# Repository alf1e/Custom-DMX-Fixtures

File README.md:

# Alfie's Custom DMX Fixtures
## What is this?
This project contains any relevant files for Custom DMX Fixtures project. In this repository you can find a PCB controller board, compatible with Neopixel LEDs using WLED. A fixture board which converts the signal sent from the controller to something usable by the Neopixel strip. And a LED Bar Fixture using the 24V version of the fixture control board.

## Why did you make this?
I volunteer at my school running our lighting rig for our shows. After one show in February, I realised something was missing and that it would look awesome with some kind of bar fixture. So I started this project and here we are now :D

# Images
Here are some relevant pictures of my project. Ill add more as I have then and as is needed.

## Control Board

## 24V Fixture Board

# Firmware
For the firmware, you can use any compilation of WLED with DMX enabled.

You can compile WLED at [this website](https://wled-compile.github.io/?lang=en) using my config file in the root of this repository called `firmware.json`

# External Wiring
A DMX Fixture is basically a fancy name for a software controlled light, usually in a theatrical setting. My Fixtures are connected to the controlled using a GX12-4 cable matching 24V with 24V, A with LED-, B with LED+ and GND with GND. Relatively simple!

# How to use.
Once you have the firmware installed there is 2 ways you can use this.

## No DMX
This can be purely controlled by any WLED control software. For mobile, I use WLED Native or just go to the IP of the controller on desktop. You can then change the colour and set effects through here

## DMX
This is a bit more complicated. Once you have connected the controller to your computer via a DMX interface you can open any DMX control software like QLC+ and import the configuration of the lights (Coming soon! I cant create a configuration without having at least a prototype) and then you can control the lights through QLC+. Remember to make sure you have no overlapping channels though!

# BOM
The following table and `BOM.csv` file are a combination of 4x 24V LED Bar Fixtures and 1x Control Board. For the individual BOMs see `BOM.md`

**Total BOM Cost: $223.09**

|Mrf#                  |Mfr.                        |Order Qty.|Unit Price(USD)|Ext.Price(USD)|LCSC#    |Package                         |Min|Mult|SPQ |Availability|Stock Status|Customer Notes|Description                                                                                                                 |Product Link                                                                                                                                                                                                                                                                                                                                                                                                                                                                                                                                                  |
|----------------------|----------------------------|----------|---------------|--------------|---------|--------------------------------|---|----|----|------------|------------|--------------|----------------------------------------------------------------------------------------------------------------------------|--------------------------------------------------------------------------------------------------------------------------------------------------------------------------------------------------------------------------------------------------------------------------------------------------------------------------------------------------------------------------------------------------------------------------------------------------------------------------------------------------------------------------------------------------------------|
|TZ-L2-03YYBG2TDJ30-002|TUOZHAN                     |20        |0.0213         |0.43          |C779432  |Through Hole,D=3mm              |20 |20  |1000|300         |In Stock    |              |Emerald Green 3mm Round Lens Through Hole,D=3mm LED Indication - Discrete ROHS                                              |https://lcsc.com/product-detail/led-indication-discrete_tuozhan-tz-l2-03yybg2tdj30-002_C779432.html                                                                                                                                                                                                                                                                                                                                                                                                                                                           |
|NUP2105L              |(DIOTEC)                    |10        |0.0899         |0.9           |C3700834 |SOT-23-3                        |5  |5   |3000|45          |In Stock    |              |8A@8/20us 350W 44V 26.2V 24V SOT-23-3 ESD and Surge Protection (TVS/ESD) ROHS                                               |https://lcsc.com/product-detail/esd-and-surge-protection-tvs-esd_diotec-nup2105l_C3700834.html                                                                                                                                                                                                                                                                                                                                                                                                                                                                |
|178.6165.0002         |Littelfuse                  |4         |2.1355         |8.54          |C207061  |Through Hole                    |1  |1   |500 |2007        |In Stock    |              |Through Hole Fuseholders ROHS                                                                                               |https://lcsc.com/product-detail/fuseholders_littelfuse-178-6165-0002_C207061.html                                                                                                                                                                                                                                                                                                                                                                                                                                                                             |
|DB302-5.0-3P-GN-S     |DORABO                      |5         |0.2851         |1.43          |C2997276 |P=5mm                           |5  |5   |500 |1085        |In Stock    |              |1x3P -40℃~+105℃ 30A 300V Green Through Hole 5mm 1 3 P=5mm Screw Terminal Blocks ROHS                                        |https://lcsc.com/product-detail/screw-terminal-blocks_dorabo-db302-5-0-3p-gn-s_C2997276.html                                                                                                                                                                                                                                                                                                                                                                                                                                                                  |
|2.54-1*4P             |BOOMELE(Boom Precision Elec)|20        |0.0469         |0.94          |C2718488 |Through Hole,P=2.54mm           |10 |10  |1000|38270       |In Stock    |              |2.54mm 1 3A 4P Bronze -40℃~+105℃ Through Hole 1x4P Top Square Hole Through Hole,P=2.54mm Female Headers ROHS                |https://lcsc.com/product-detail/female-headers_boomele-boom-precision-elec-2-54-1-4p_C2718488.html                                                                                                                                                                                                                                                                                                                                                                                                                                                            |
|PM254-1-19-Z-8.5      |HCTL                        |5         |0.3055         |1.53          |C2897382 |Through Hole,P=2.54mm           |5  |5   |120 |6380        |In Stock    |              |2.54mm 1 3A Copper Alloy 19P -40℃~+105℃ Through Hole 1x19P 8.5mm Top Square Hole Through Hole,P=2.54mm Female Headers ROHS  |https://lcsc.com/product-detail/female-headers_hctl-pm254-1-19-z-8-5_C2897382.html                                                                                                                                                                                                                                                                                                                                                                                                                                                                            |
|ZX-PZ2.54-1-1PZZ      |Megastar                    |20        |0.0116         |0.23          |C7501259 |Through Hole,P=2.54mm           |20 |20  |2000|33300       |In Stock    |              |Gold 3A Through Hole Pin Header 2.5mm 1P 6mm -40℃~+105℃ 3mm 2.54mm Brass Black 1 1x1P Through Hole,P=2.54mm Pin Headers ROHS|https://lcsc.com/product-detail/pin-headers_megastar-zx-pz2-54-1-1pzz_C7501259.html                                                                                                                                                                                                                                                                                                                                                                                                                                                                           |
|DB302-5.0-4P-GN-S     |DORABO                      |8         |0.4435         |3.55          |C5143708 |Through Hole,P=5mm              |1  |1   |200 |647         |In Stock    |              |20A 1x4P -40℃~+105℃ 300V Green Through Hole 5mm 1 4 Through Hole,P=5mm Screw Terminal Blocks ROHS                           |https://lcsc.com/product-detail/screw-terminal-blocks_dorabo-db302-5-0-4p-gn-s_C5143708.html                                                                                                                                                                                                                                                                                                                                                                                                                                                                  |
|MFR-25FTE52-4K7       |YAGEO                       |50        |0.0117         |0.59          |C173023  |Through Hole,D2.4xL6.3mm        |50 |50  |5000|62150       |In Stock    |              |Metal Film Resistor 4.7kΩ 250mW ±50ppm/℃ ±1% Through Hole,D2.4xL6.3mm Through Hole Resistors ROHS                           |https://lcsc.com/product-detail/through-hole-resistors_yageo-mfr-25fte52-4k7_C173023.html                                                                                                                                                                                                                                                                                                                                                                                                                                                                     |
|0287002.PXCN          |Littelfuse                  |5         |0.1083         |0.54          |C142680  |-                               |5  |5   |2000|2320        |In Stock    |              |32V 1kA Blade Fuse 2A Automotive Fuses ROHS                                                                                 |https://lcsc.com/product-detail/automotive-fuses_littelfuse-0287002-pxcn_C142680.html                                                                                                                                                                                                                                                                                                                                                                                                                                                                         |
|DC-508-ARL250-H069    |XUNPU                       |1         |1.3904         |1.39          |C34388679|Through Hole                    |1  |1   |400 |357         |In Stock    |              |Right Angle DC Power Jack -40℃~+85℃ 2.5mm 5.7mm 20A 30V Through Hole DC Power Connectors ROHS                               |https://lcsc.com/product-detail/dc-power-connectors_xunpu-dc-508-arl250-h069_C34388679.html                                                                                                                                                                                                                                                                                                                                                                                                                                                                   |
|S3B-EH(LF)(SN)        |JST                         |10        |0.0458         |0.46          |C263754  |Through Hole,Right Angle,P=2.5mm|10 |10  |1000|60          |In Stock    |              |1x3P 3P EH Tin 3 -25℃~+85℃ 3A 1 2.5mm Brass Right Angle Through Hole,Right Angle,P=2.5mm Wire To Board Connector ROHS       |https://lcsc.com/product-detail/wire-to-board-connector_jst-s3b-eh-lf-sn_C263754.html                                                                                                                                                                                                                                                                                                                                                                                                                                                                         |
|-                     |-                           |5         |0.98           |4.9           |-        |-                               |-  |-   |-   |-           |-           |              |LM2596                                                                                                                      |https://www.aliexpress.com/item/1005004904872120.html?spm=a2g0o.productlist.main.1.648c541bqH9rJl&algo_pvid=3365030b-ba65-48ef-b795-25a7323940d2&algo_exp_id=3365030b-ba65-48ef-b795-25a7323940d2-0&pdp_ext_f=%7B%22order%22%3A%224923%22%2C%22eval%22%3A%221%22%7D&pdp_npi=4%40dis%21GBP%210.98%210.98%21%21%211.31%211.31%21%40210385a817511532162265793e9d93%2112000030968453860%21sea%21UK%216246721987%21X&curPageLogUid=SCB0lC5DUt0Q&utparam-url=scene%3Asearch%7Cquery_from%3A                                                                         |
|-                     |-                           |9         |0.28           |2.52          |-        |-                               |-  |-   |-   |-           |-           |              |RS-485 TTL                                                                                                                  |https://www.aliexpress.com/item/1005005737922222.html?spm=a2g0o.cart.0.0.29fc38dazYWvCI&mp=1&pdp_npi=5%40dis%21GBP%21GBP%202.28%21GBP%201.49%21%21GBP%201.49%21%21%21%402103846917511531537767901edbce%211200004452696347                                                                                                                                                                                                                                                                                                                                     |
|-                     |-                           |1         |3.42           |3.42          |-        |-                               |-  |-   |-   |-           |-           |              |ESP32-DevKitC                                                                                                               |https://www.aliexpress.com/item/1005007820190456.html?spm=a2g0o.productlist.main.1.3c437abdXeRiKL&algo_pvid=a9f971fb-d5f2-470f-8ec5-9bb780a11c0e&algo_exp_id=a9f971fb-d5f2-470f-8ec5-9bb780a11c0e-0&pdp_ext_f=%7B%22order%22%3A%22911%22%2C%22eval%22%3A%221%22%7D&pdp_npi=4%40dis%21GBP%212.21%211.49%21%21%2121.10%2114.22%21%4021038da617511538383186262ec7d4%2112000042325137321%21sea%21UK%216246721987%21X&curPageLogUid=NeRNsyLEpTQ8&utparam-url=scene%3Asearch%7Cquery_from%3A                                                                        |
|-                     |-                           |1         |13.4           |13.4          |-        |-                               |-  |-   |-   |-           |-           |              |Control Board PCB                                                                                                           |                                                                                                                                                                                                                                                                                                                                                                                                                                                                                                                                                              |
|-                     |-                           |4         |6              |24            |-        |-                               |-  |-   |-   |-           |-           |              |24V Fixture PCB                                                                                                             |                                                                                                                                                                                                                                                                                                                                                                                                                                                                                                                                                              |
|-                     |-                           |4         |20.21          |80.84         |-        |-                               |-  |-   |-   |-           |-           |              |Polycarbonate Tube                                                                                                          |https://www.ebay.co.uk/itm/276693351932?_skw=frosted+round+rigid+polycarbonate+tube&itmmeta=01K04KKFDF3AJ286QVF0MJMHY5&hash=item406c357dfc%3Ag%3AltAAAOSwSiBnE-rc&itmprp=enc%3AAQAKAAAA4FkggFvd1GGDu0w3yXCmi1f7aXwdpIx9IYPY3Br8vi7vcu88WAFKXgSIObTo99wU94qLx%2F4q%2B8mSy8yiOFfK2O9yquNEseovPOWru4rv4ONDsM%2FCkBpKu4MNbLXtH8TfDre93db7qzknJPlWCpg3coSkv4xKbH2xQ5bO3E0Tuu97E%2F3SG4%2FbP1yk3JdD4ooG5DHvHmOt1lcXt3%2F71JB3%2FbCF74wIcgGMwe5mazzk4QTK2%2B6wlIg3E3qEpVTSkJJrFB8WyLjw0a2LjLRXMIImqgTV%2BJngFIAjqnugciSfxVUS%7Ctkp%3ABk9SR-72zZOBZg&var=2560126467598|
|-                     |-                           |4         |14.57          |58.28         |-        |-                               |-  |-   |-   |-           |-           |              |WS2811-COB                                                                                                                  |https://www.aliexpress.com/item/1005008502347105.html?algo_exp_id=5c1c1235-e70a-4246-a32f-a700219098fe-4&pdp_ext_f=%7B%22order%22%3A%2231%22%2C%22eval%22%3A%221%22%7D&pdp_npi=4%40dis!GBP!10.65!5.05!!!14.16!6.72!%4021038df617509815831908318e4312!12000045561188117!sea!UK!0!ABX&curPageLogUid=G9q3zAPoAXfc&utparam-url=scene%3Asearch%7Cquery_from%3A                                                                                                                                                                                                     |
|-                     |-                           |1         |10.99          |10.99         |-        |-                               |-  |-   |-   |-           |-           |              |24V 10A PSU                                                                                                                 |https://www.aliexpress.com/item/1005005763465796.html?spm=a2g0o.cart.0.0.155638darvq6KW&mp=1&pdp_npi=5%40dis%21GBP%21GBP%208.33%21GBP%208.33%21%21GBP%208.33%21%21%21%402103963717533502035943943e99db%2112000034265307623%21ct%21UK%216246721987%21%211%210                                                                                                                                                                                                                                                                                                  |
|-                     |-                           |1         |3.04           |3.04          |-        |-                               |-  |-   |-   |-           |-           |              |DMX Input                                                                                                                   |https://www.aliexpress.com/item/1005007432049215.html?spm=a2g0o.productlist.main.5.16547d36LxjoCa&algo_pvid=45811b24-a078-4e17-af7d-c0fac50111f5&algo_exp_id=45811b24-a078-4e17-af7d-c0fac50111f5-4&pdp_ext_f=%7B%22order%22%3A%22289%22%2C%22eval%22%3A%221%22%7D&pdp_npi=4%40dis%21USD%213.04%213.04%21%21%213.04%213.04%21%40211b815c17533503935243532e9857%2112000040758600589%21sea%21UK%216246721987%21X&curPageLogUid=vV8bw7n6iAWJ&utparam-url=scene%3Asearch%7Cquery_from%3A                                                                          |
|-                     |-                           |8         |0.32           |2.56          |-        |-                               |-  |-   |-   |-           |-           |              |Fixture Connectors                                                                                                          |https://www.aliexpress.com/item/1005002920441877.html?spm=a2g0o.productlist.main.17.43a51e24Vo5Vvb&algo_pvid=c1b3e4c4-fd95-47fd-973d-1b4b3ff86cb8&algo_exp_id=c1b3e4c4-fd95-47fd-973d-1b4b3ff86cb8-16&pdp_ext_f=%7B%22order%22%3A%2212%22%2C%22eval%22%3A%221%22%7D&pdp_npi=4%40dis%21USD%210.16%210.12%21%21%210.16%210.12%21%40210384cc17533504720682578efd31%2112000022803273504%21sea%21UK%216246721987%21X&curPageLogUid=EQ0dn1qLd6nB&utparam-url=scene%3Asearch%7Cquery_from%3A                                                                         |

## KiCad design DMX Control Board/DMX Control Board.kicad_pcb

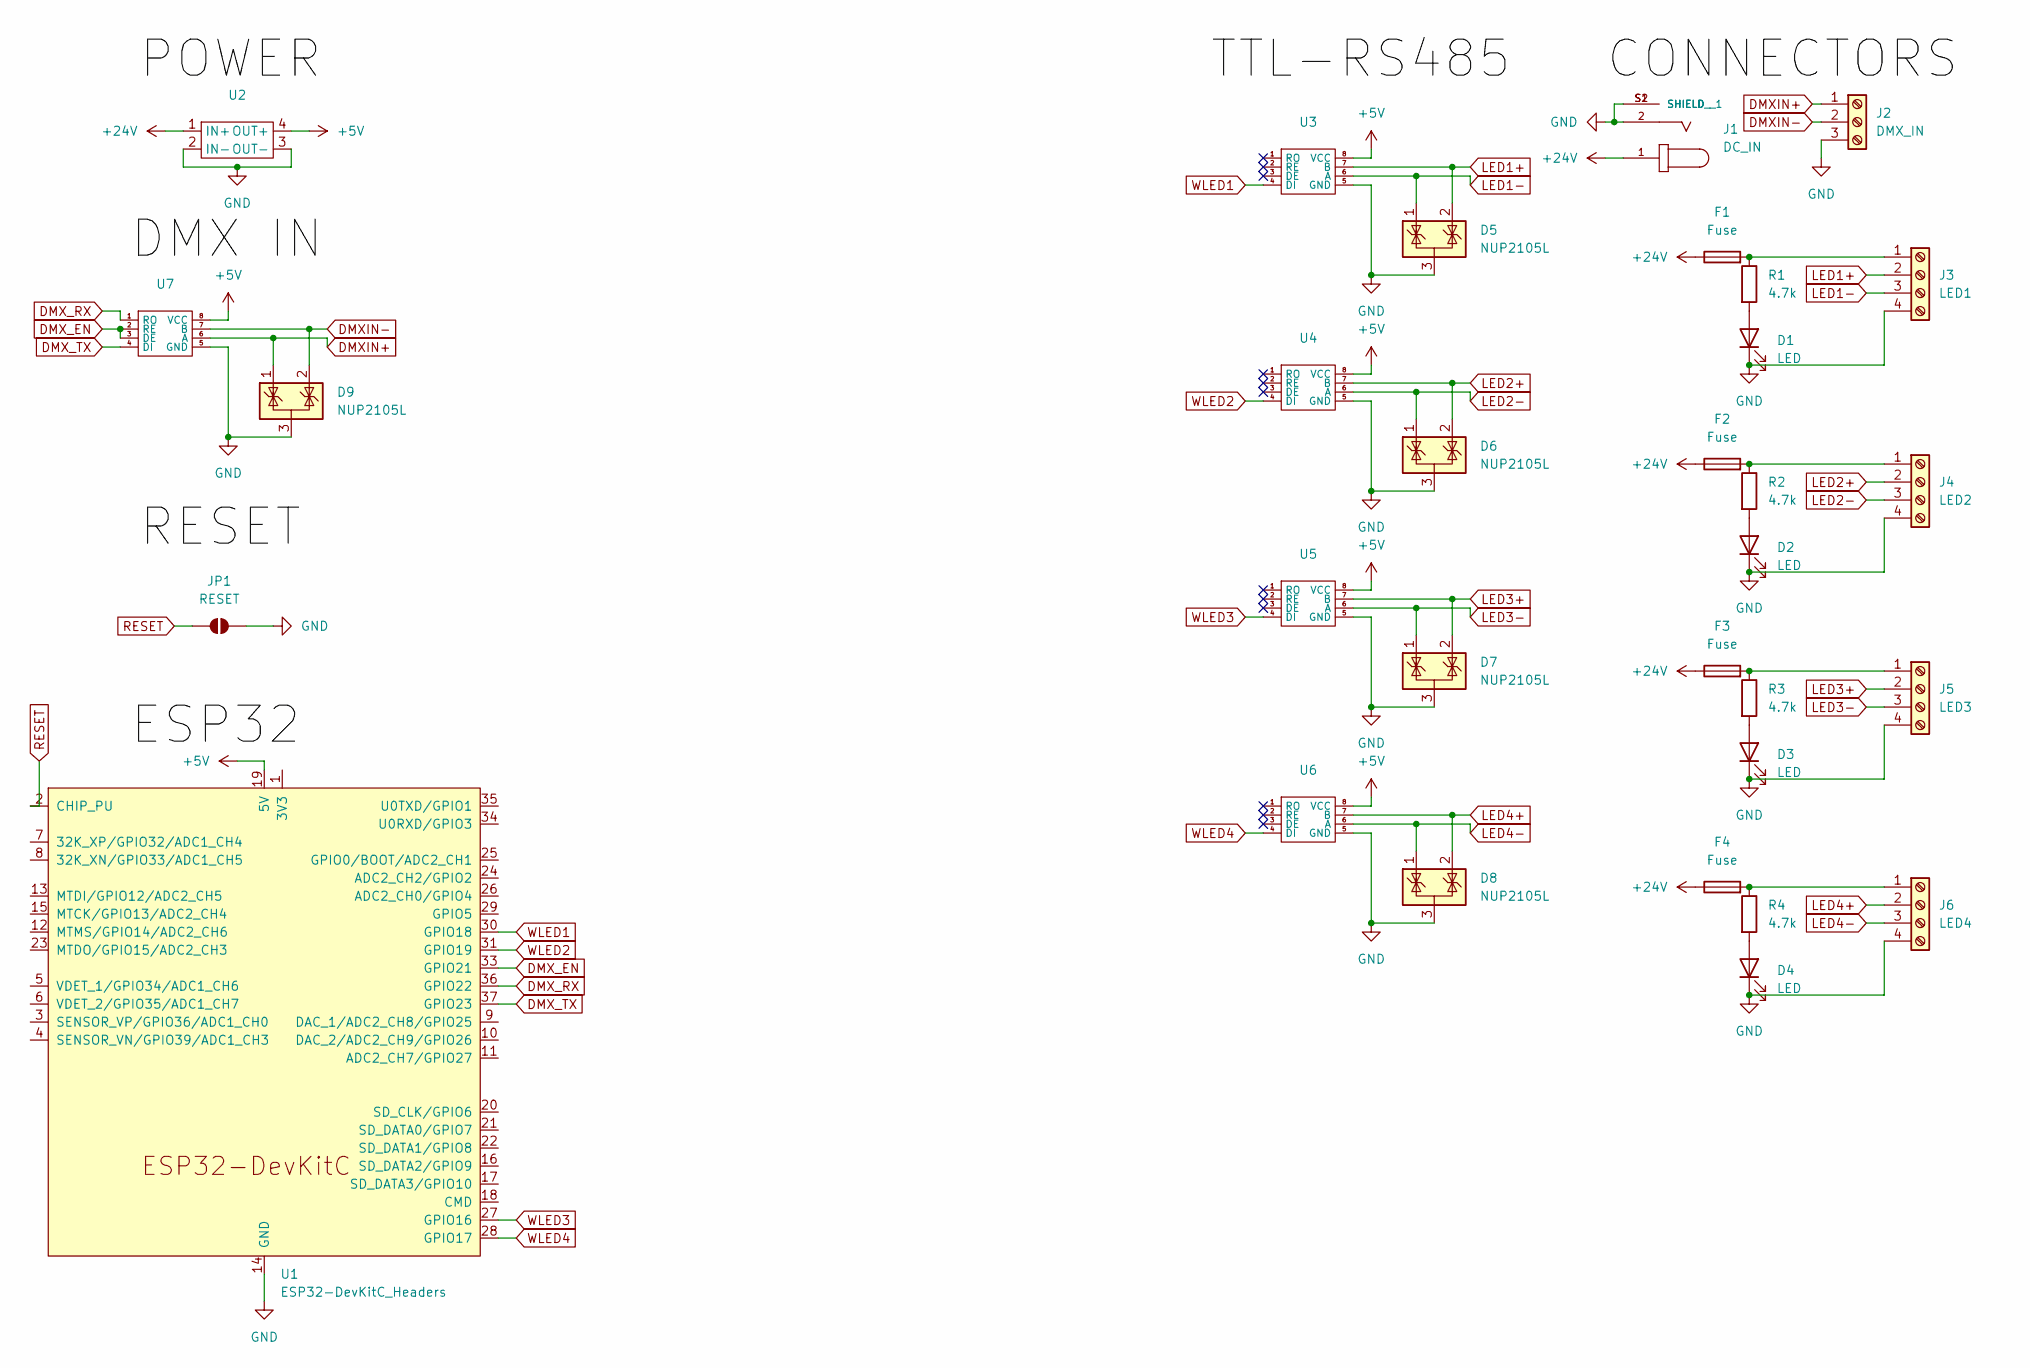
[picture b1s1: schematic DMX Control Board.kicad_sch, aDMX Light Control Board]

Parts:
D1, D2, D3, D4: LED; LED_D3.0mm
D5, D6, D7, D8, D9: NUP2105L; SOT-23
F1, F2, F3, F4: Fuse; FuseHolder_Blade_ATO_Littelfuse_FLR_178.6165
J1: DC_IN; CUI_PJ-063AH; PARTREV 1.02
J2: DMX_IN; TerminalBlock_MetzConnect_Type011_RT05503HBWC_1x03_P5.00mm_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
J3: LED1; TerminalBlock_MetzConnect_Type011_RT05504HBWC_1x04_P5.00mm_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
J4: LED2; TerminalBlock_MetzConnect_Type011_RT05504HBWC_1x04_P5.00mm_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
J5: LED3; TerminalBlock_MetzConnect_Type011_RT05504HBWC_1x04_P5.00mm_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
J6: LED4; TerminalBlock_MetzConnect_Type011_RT05504HBWC_1x04_P5.00mm_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
JP1: RESET; SolderJumper-2_P1.3mm_Open_RoundedPad1.0x1.5mm
R1, R2, R3, R4: 4.7k; R_Axial_DIN0204_L3.6mm_D1.6mm_P5.08mm_Horizontal
U1: ESP32-DevKitC_Headers
U2: LM2596S-Buck-Module
U3, U4, U5, U6, U7: Max485

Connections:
+5V: U1.19 (5V), U2.4 (OUT+), U3.8 (VCC), U4.8 (VCC), U5.8 (VCC), U6.8 (VCC), U7.8 (VCC)
+24V: F1.1, F2.1, F3.1, F4.1, J1.1, U2.1 (IN+)
DMXIN+: D9.1 (K), J2.1, U7.6 (A)
DMXIN-: D9.2 (K), J2.2, U7.7 (B)
DMX_EN: U1.33 (GPIO21), U7.2 (RE), U7.3 (DE)
DMX_RX: U1.36 (GPIO22), U7.1 (RO)
DMX_TX: U1.37 (GPIO23), U7.4 (DI)
GND: D1.1 (K), D2.1 (K), D3.1 (K), D4.1 (K), D5.3 (A), D6.3 (A), D7.3 (A), D8.3 (A), D9.3 (A), J1.2, J1.S1 (SHIELD), J1.S2 (SHIELD__1), J2.3, J3.4, J4.4, J5.4, J6.4, JP1.2 (B), U1.14 (GND), U1.32 (GND), U1.38 (GND), U2.2 (IN-), U2.3 (OUT-), U3.5 (GND), U4.5 (GND), U5.5 (GND), U6.5 (GND), U7.5 (GND)
LED1+: D5.2 (K), J3.2, U3.7 (B)
LED1-: D5.1 (K), J3.3, U3.6 (A)
LED2+: D6.2 (K), J4.2, U4.7 (B)
LED2-: D6.1 (K), J4.3, U4.6 (A)
LED3+: D7.2 (K), J5.2, U5.7 (B)
LED3-: D7.1 (K), J5.3, U5.6 (A)
LED4+: D8.2 (K), J6.2, U6.7 (B)
LED4-: D8.1 (K), J6.3, U6.6 (A)
unnamed: D1.2 (A), R1.2
unnamed: D2.2 (A), R2.2
unnamed: D3.2 (A), R3.2
unnamed: D4.2 (A), R4.2
unnamed: F1.2, J3.1, R1.1
unnamed: F2.2, J4.1, R2.1
unnamed: F3.2, J5.1, R3.1
unnamed: F4.2, J6.1, R4.1
RESET: JP1.1 (A), U1.2 (CHIP_PU)
WLED1: U1.30 (GPIO18), U3.4 (DI)
WLED2: U1.31 (GPIO19), U4.4 (DI)
WLED3: U1.27 (GPIO16), U5.4 (DI)
WLED4: U1.28 (GPIO17), U6.4 (DI)

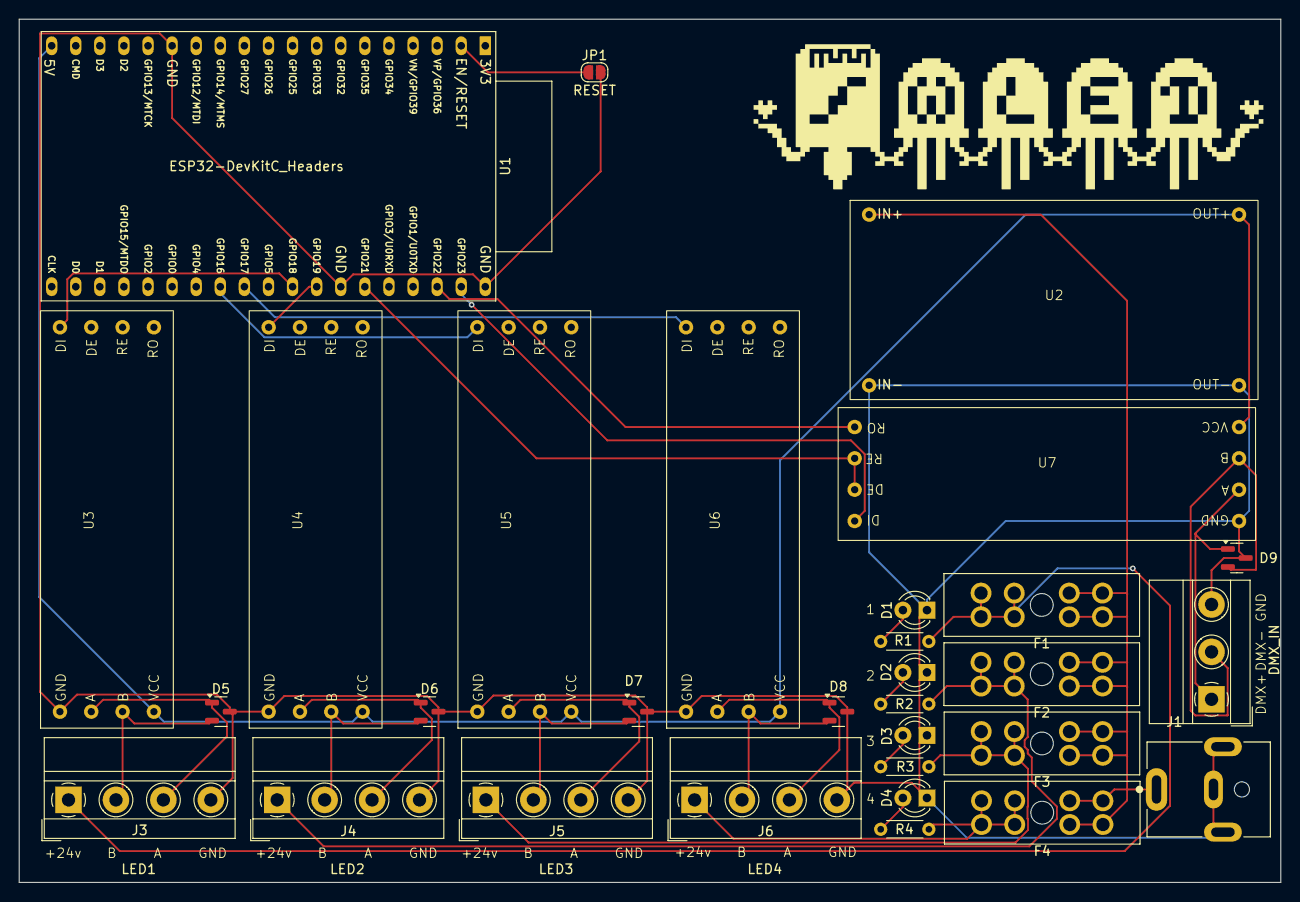
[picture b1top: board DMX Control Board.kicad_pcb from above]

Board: 2 copper layers, 133.0 x 91.0 mm, 31 parts (0 on the bottom side), 29 nets.

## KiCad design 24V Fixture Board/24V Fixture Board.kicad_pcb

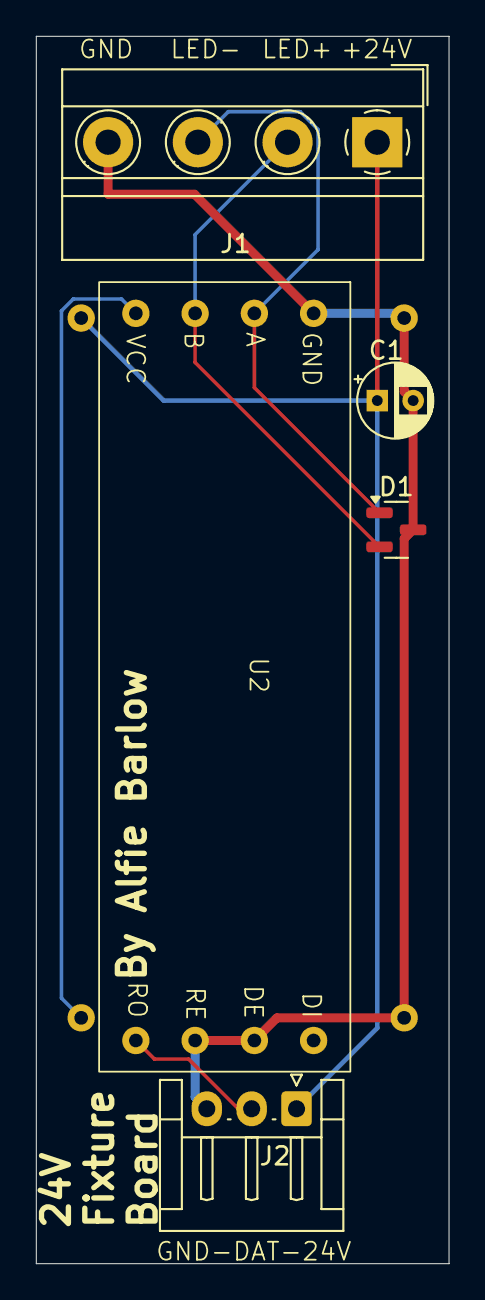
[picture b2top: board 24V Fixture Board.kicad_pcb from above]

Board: 2 copper layers, 23.0 x 68.4 mm, 6 parts (1 on the bottom side), 6 nets.

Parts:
C1: 1μF; CP_Radial_D4.0mm_P2.00mm
D1: NUP2105L; SOT-23
J1: LED_IN; TerminalBlock_MetzConnect_Type011_RT05504HBWC_1x04_P5.00mm_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
J2: Conn_01x03; JST_EH_S3B-EH_1x03_P2.50mm_Horizontal
U1: LM2596S-Buck-Module
U2: Max485

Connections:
+5V: U1.4 (OUT+), U2.8 (VCC)
+24V: C1.1, J1.1, J2.1, U1.1 (IN+)
GND: C1.2, D1.3 (A), J1.4, J2.3, U1.2 (IN-), U1.3 (OUT-), U2.2 (RE), U2.3 (DE), U2.5 (GND)
LED: J2.2, U2.1 (RO)
LED+: D1.2 (K), J1.2, U2.7 (B)
LED-: D1.1 (K), J1.3, U2.6 (A)

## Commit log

2025-06-26 Fixing Images
2025-06-26 Reorganisation
2025-06-26 Oopsie forgot some files
2025-06-26 Fix the BOM
2025-06-26 Change a name (I hope your getting used to unclear silly commit names)
2025-06-27 27/06 Dump
2025-06-27 oopsie missed time taken
2025-06-28 Add BOM
2025-06-28 Add todays work
2025-06-28 I did a boo boo with the bom bom
2025-07-14 Do some more BOMs and add models
2025-07-17 Big super-duper mega commit
2025-07-17 Fix BOM in README.md
2025-07-24 The Great Fixit
2025-07-27 27th Mega Commit
2025-07-27 Remove the test file
2025-07-31 Make Highway people happy :D
2025-07-31 and again
2025-07-31 Add wiring guide
2025-07-31 Add wiring guide image
